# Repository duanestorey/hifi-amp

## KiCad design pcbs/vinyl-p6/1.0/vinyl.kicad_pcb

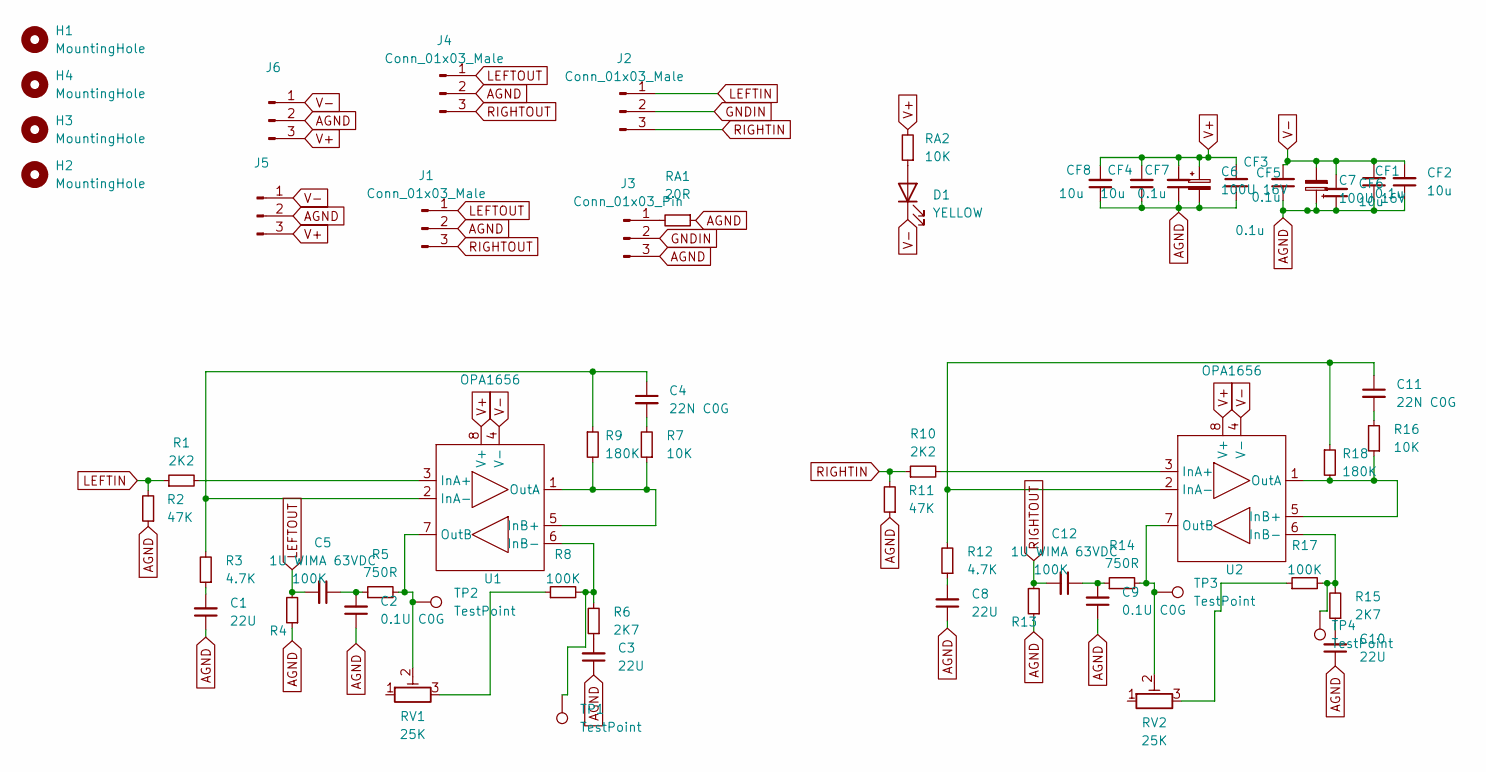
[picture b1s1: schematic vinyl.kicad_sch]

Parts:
C1, C3, C8, C10: 22U; CP_Radial_D6.3mm_P2.50mm
C2, C9: 0.1U C0G; C_1206_3216Metric_Pad1.33x1.80mm_HandSolder; Mouser 81-GRM3195C1H104GA5D
C4, C11: 22N C0G; C_0805_2012Metric_Pad1.18x1.45mm_HandSolder
C5, C12: 1U WIMA 63VDC; C_Rect_L7.2mm_W11.0mm_P5.00mm_FKS2_FKP2_MKS2_MKP2; Mouser 505-MKP2C0411NMN
C6, C7: 100U 16V; CP_Radial_D6.3mm_P2.50mm
CF1, CF3, CF5, CF7: 0.1u; C_0805_2012Metric_Pad1.18x1.45mm_HandSolder
CF2, CF4, CF6, CF8: 10u; C_1206_3216Metric_Pad1.33x1.80mm_HandSolder
D1: YELLOW; LED_0603_1608Metric_Pad1.05x0.95mm_HandSolder
H1, H2, H3, H4: MountingHole; MountingHole_3.2mm_M3_DIN965_Pad_TopOnly
J1, J2, J5, J6: Conn_01x03_Male; JST_PH_B3B-PH-K_1x03_P2.00mm_Vertical
J3: Conn_01x03_Pin; PinHeader_1x03_P2.54mm_Vertical
J4: Conn_01x03_Male; PinHeader_1x03_P2.54mm_Vertical
R1, R10: 2K2; R_0805_2012Metric_Pad1.20x1.40mm_HandSolder; Mouser 603-RT0805FRE072K2L
R2, R11: 47K; R_0805_2012Metric_Pad1.20x1.40mm_HandSolder; Mouser 603-RT0805FRE0747KL
R3, R12: 4.7K; R_0805_2012Metric_Pad1.20x1.40mm_HandSolder; Mouser 603-RT0805FRE074K7L
R4, R8, R13, R17: 100K; R_0805_2012Metric_Pad1.20x1.40mm_HandSolder; Mouser 603-RT0805FRE10100KL
R5, R14: 750R; R_0805_2012Metric_Pad1.20x1.40mm_HandSolder; Mouser 603-RT0805FRE07750RL
R6, R15: 2K7; R_0805_2012Metric_Pad1.20x1.40mm_HandSolder; Mouser 603-RT0805FRE072K7L
R7, R16: 10K; R_0805_2012Metric_Pad1.20x1.40mm_HandSolder; Mouser 603-RT0805FRE1310KL
R9, R18: 180K; R_0805_2012Metric_Pad1.20x1.40mm_HandSolder; Mouser 603-RT0805FRE07180KL
RA1: 20R; R_0603_1608Metric
RA2: 10K; R_0603_1608Metric
RV1, RV2: 25K; Potentiometer_Bourns_3296W_Vertical
TP1, TP2, TP3, TP4: TestPoint; TestPoint_THTPad_1.5x1.5mm_Drill0.7mm
U1, U2: OPA1656; DIP-8_W7.62mm_Socket; Mouser 595-OPA1656IDR

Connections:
AGND: C1.1, C2.1, C3.1, C6.2, C7.1, C8.1, C9.1, C10.1, CF1.1, CF2.1, CF3.1, CF4.1, CF5.1, CF6.1, CF7.1, CF8.1, J1.2, J3.3, J4.2, J5.2, J6.2, R2.1, R4.1, R11.1, R13.1, RA1.1
GNDIN: J2.2, J3.2
LEFTIN: J2.1, R1.1, R2.2
LEFTOUT: C5.2, J1.1, J4.1, R4.2
unnamed: C1.2, R3.1
unnamed: C2.2, C5.1, R5.1
unnamed: C3.2, R6.1
unnamed: C4.2, R7.2
unnamed: C8.2, R12.1
unnamed: C10.2, R15.1
unnamed: C11.2, R16.2
unnamed: C9.2, C12.1, R14.1
unnamed: D1.2 (A), RA2.1
unnamed: J3.1, RA1.2
unnamed: R8.1, RV1.3
unnamed: R17.1, RV2.3
unnamed: R1.2, U1.3 (InA+)
unnamed: C4.1, R3.2, R9.1, U1.2 (InA-)
unnamed: R7.1, R9.2, U1.1 (OutA), U1.5 (InB+)
unnamed: R6.2, R8.2, TP1.1, U1.6 (InB-)
unnamed: R5.2, RV1.2, TP2.1, U1.7 (OutB)
unnamed: R10.2, U2.3 (InA+)
unnamed: C11.1, R12.2, R18.1, U2.2 (InA-)
unnamed: R16.1, R18.2, U2.1 (OutA), U2.5 (InB+)
unnamed: R15.2, R17.2, TP4.1, U2.6 (InB-)
unnamed: R14.2, RV2.2, TP3.1, U2.7 (OutB)
RIGHTIN: J2.3, R10.1, R11.2
RIGHTOUT: C12.2, J1.3, J4.3, R13.2
V+: C6.1, CF3.2, CF4.2, CF7.2, CF8.2, J5.3, J6.3, RA2.2, U1.8 (V+), U2.8 (V+)
V-: C7.2, CF1.2, CF2.2, CF5.2, CF6.2, D1.1 (K), J5.1, J6.1, U1.4 (V-), U2.4 (V-)

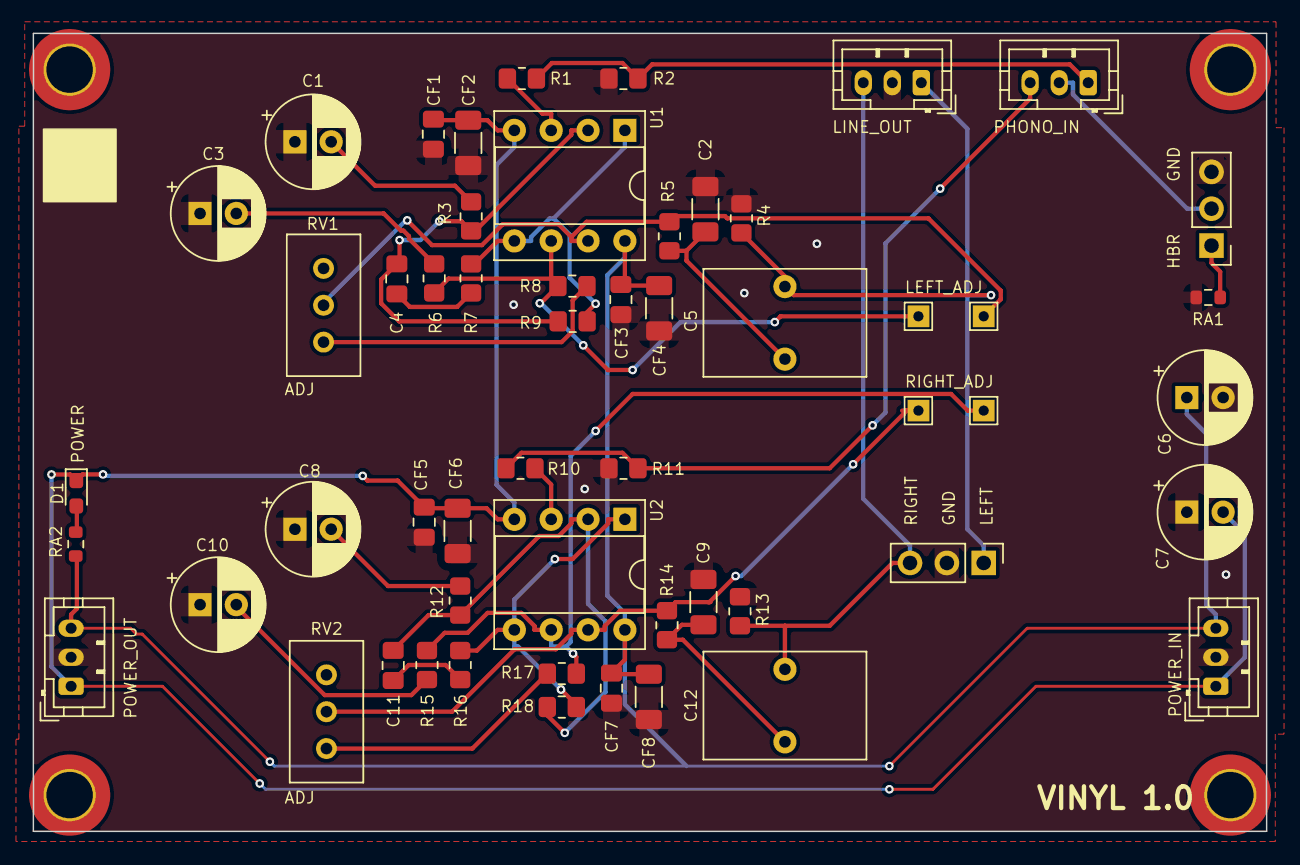
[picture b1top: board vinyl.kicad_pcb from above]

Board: 2 copper layers, 85.0 x 55.0 mm, 59 parts (0 on the bottom side), 30 nets.
